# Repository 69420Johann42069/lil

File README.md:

# Farbmischer

Ein Geschenk: Tischgerät plus Web-App. Sie wählt eine Farbe am Handy (Farbwähler oder Foto antippen), das Gerät dosiert die passenden Mengen aus fünf günstigen Acryl-Grundfarben in einen Becher, sie rührt um. Gemerkte Farben lassen sich später exakt nachmischen.

## Entscheidungen

- Acrylfarbe aus fünf 60-ml-Spritzen: Primär-Cyan, Primär-Magenta, Primär-Gelb, Titanweiß, Schwarz
- Günstige Studienacryl in 500-ml-Flaschen als Vorrat, nachgefüllt wird direkt in die Spritze
- Bauform Stand 6: schwarzer Flakon mit Goldlinien, Ø 204 mm, 407 mm hoch, sechs Spritzen im Karussell, zwei Schrittmotoren, Dosieren nach Gewicht mit Wägezelle, Becher in einer Schublade. Ohne Licht, alles aus PETG gedruckt (auch Gold und Scheiben), keine Lackierung
- Bedienung nur im Browser, der ESP32 liefert die Seite selbst im WLAN aus
- Gerät dosiert nur, kein Rührwerk
- Elektronik auf Lochraster (zwei Treiber), Druckteile aus dem eigenen Drucker (Anycubic Kobra 2 Pro) in PETG

## Aufbau des Repos

| Pfad | Inhalt |
|---|---|
| `web/` | Web-App: Farbwahl, Foto, Rezept, gemerkte Farben, Kalibrierung, Gerätesteuerung |
| `firmware/` | PlatformIO-Projekt für den ESP32 |
| `hardware/` | Parameterblätter, OpenSCAD-Druckteile und Renderings (aktuell: Flakon Stand 8) |
| `electronics/` | `VERDRAHTUNG.md`: Verdrahtungsplan Stand 8 (Lochraster, Dupont). Die alte KiCad-Trägerplatine (Fünf-Motor-Variante) gilt nicht mehr |

## Stufen

| Stufe | Was | Status |
|---|---|---|
| 0 | Web-App: Farbe wählen, Rezept in Gramm, mit Küchenwaage abwiegen | fertig, getestet |
| 1 | Flakon mit zwei Motoren und Spritzenkarussell | Stand 8: Druckteile (OpenSCAD), Rendering, 56 Kollisionsprüfungen, Firmware (zwei Motoren, Wägezelle, Hall, Dosieren nach Gewicht, Host-Test der Rechenfunktionen), Web-App und Verdrahtungsplan fertig, Build mit `pio run` und alles auf Hardware nicht getestet |
| 2 | Kalibrierung mit Farbsensor | optional |

## Stufe 0: Web-App

1. `mixbox.js` herunterladen und nach `web/` legen. Quelle: Repository `scrtwpns/mixbox` auf GitHub, Datei `javascript/mixbox.js`. Lizenz CC BY-NC 4.0, für ein privates Geschenk in Ordnung, nicht für Verkauf. Die Datei steht in `.gitignore`.
2. `web/index.html` im Browser öffnen. Für das Handy im gleichen WLAN:

```
cd web
python3 -m http.server 8000
```

Dann am Handy `http://<IP des Rechners>:8000` aufrufen.

Funktionen: Farbwähler oder Hex-Wert, Farbe aus einem Foto antippen (Handykamera), Gesamtmenge in Gramm, Rezept mit Vorhersage-Swatch und Abweichung, Farben mit Namen merken und wieder laden, Primärfarben kalibrieren, Gerät steuern.

Die Farbmathematik liegt in `web/farbmath.js`: Mixbox mischt die Primärfarben im Latentraum, ein projizierter Gradientenabstieg sucht die Anteile mit kleinster Lab-Abweichung zur Zielfarbe.

### Primärfarben kalibrieren

Jede Grundfarbe satt auf weißes Papier streichen, trocknen lassen, bei Tageslicht fotografieren, Farbwert mit einer Pipette ablesen und in der App eintragen. Das verbessert die Rezepte deutlich, weil die Standardwerte nur grobe Schätzungen sind.

## Farben kaufen

Fünf Flaschen reichen für alles. Gesucht wird in Studienqualität (Flasche 250 bis 500 ml, meist unter 10 Euro):

| Spritze | Farbe | Suchbegriff beim Händler |
|---|---|---|
| C | Primär-Cyan | Primary Cyan, Primärblau, Cyan |
| M | Primär-Magenta | Primary Magenta, Primärrot, Magenta |
| Y | Primär-Gelb | Primary Yellow, Primärgelb |
| W | Titanweiß | Titanium White |
| K | Schwarz | Ivory Black oder Mars Black |

Nachfüllen: Kolben aus der Spritze ziehen, Farbe aus der Flasche einfüllen, Kolben wieder einsetzen, Düse nach oben, Luft rausdrücken. Flaschenfarbe ist dünner als Tubenfarbe und pumpt sich leichter.

## Stand 6: Flakon aus PETG, ohne Licht (aktuelles Konzept)

Entstanden aus der Kritik von vier Rollen (Kosten, Design, Ingenieur, Kunstliebhaberin), drei Konzepten und deren Bewertung (Stand 5.1), dann umgebaut auf den Wunsch „fast alles 3D-druckbar, keine LEDs, PETG“. Maßgeblich ist `hardware/farbmischer_parameter.md` mit Stückliste, Verdrahtung und dem Abschnitt für die Firmware. Rendering: `hardware/rendering_farbmischer.png`, Kollisionsprüfung: `python3 hardware/render_farbmischer.py --pruefung`, Druckteile: `hardware/farbmischer.scad` (Variable `teil`, jedes Teil liegt in Druckorientierung auf Z = 0; `openscad -o teil.stl -D 'teil="krone"' hardware/farbmischer.scad`). Gerät etwa 160 Euro, mit Startpaket und Farbe etwa 246 Euro.

Was sich gegenüber Stand 5.1 ändert: LEDs entfallen komplett (der Fortschritt steht nur in der App). Alles ist PETG, kein Spachteln, kein Lack, kein Anreibewachs. Gold sind gedruckte Gold-PETG-Teile (Goldring, Goldband, Kronenring, Portalrahmen in drei Leistenarten, Lippe, Buchsenring, Namensschild-Schrift). Portalscheibe (zwei Hälften) und Fensterscheiben sind gedruckt (Rauch- und Klar-PETG), der Ausleger mit Stempel ersetzt den Winkelstahl. Die Teilung des Körpers bei Z 235 ist eine gewollte Schattenfuge. Details in Abschnitt 0 des Parameterblatts.

**Stand 8 (Karussell direkt am Motor, Standard in `farbmischer.scad`):** Motor 2 sitzt mittig unter der Karussellplatte in einem gedruckten Kasten (Motorturm), kein Riemen, keine Welle, kein 70-Z-Rad, keine Pancake (beide Motoren sind derselbe NEMA 17, 34 mm). Filament zählt nicht mit. Aufbau auf Stand 7:

Schnelles Rendering Stand 8 (aus den OpenSCAD-Teilen, Scheiben undurchsichtig dargestellt): `hardware/rendering_stand8_aussen.png` und `hardware/rendering_stand8_schnitt.png` (Längsschnitt, Motorturm blau).

**Stand 7 Budget** (Schalter `budget`): ohne Feuchtrinne, Magnete an den Scheiben, gekaufte Linearlager und Gewindeeinsätze (Linearlager sind gedruckt, Ballast wird gratis mit Schrauben aus dem Arbeitsvorrat gefüllt; Portalscheiben, Fensterscheiben, Goldrahmen und Goldlippe bleiben, sie sind gedruckt und kosten nichts extra, die Scheiben werden geklebt), Gerät etwa 83 Euro, alles zusammen etwa 164 Euro, ohne Filament, Schrauben, Muttern, Scheiben und Kleber aus dem Arbeitsvorrat. Einkauf bei einem Shop (Amazon.de, Links, Preise teils unbelegt): `hardware/einkaufsliste_amazon.md`. Einkaufsliste mit Quellen und gekennzeichneten Schätzungen: `hardware/einkaufsliste.md`.

Filament für das ganze Gerät (Stand 6): PETG schwarz etwa 1,4 kg (am besten glänzend für Sockel und Front, matt für Körper und Krone), Gold 35 g, Rauch-PETG 50 g, Klar-PETG 25 g, weiß 40 g.

## Stufe 1: Revolver (Stand 4, abgelöst)

Zwei Schrittmotoren, fünf Spritzen in einem Karussell. Der Stößel sitzt fest über der vorderen Station, ein zweiter Motor zentral im Sockel dreht das Karussell direkt über eine Welle in der Mitte. Die Nutzerin wählt die Farbe, das Gerät dreht und dosiert alle Stationen nacheinander, am Ende nimmt sie den Becher heraus und rührt um. Säule Ø 170 mm, 48 cm hoch, Fenster unten vorne für den Becher, Rändelrand des Karussells durch einen Schlitz drehbar. Parameterblatt: `hardware/revolver_parameter.md`, Druckteile: `hardware/revolver.scad`, Rendering: `hardware/rendering_revolver.png`.

Vorbild aus der Recherche: das Hackaday-Projekt If Then Paint nutzt ein Spritzenkarussell mit fester Druckplatte (https://hackaday.io/project/166524). Zwei Lehren daraus: die Druckplatte darf nicht freitragend sein (dort hat sie sich bei 30-ml-Spritzen verbogen), und Acrylfarbe ist thixotrop, also nach dem Dosieren kurz warten, bevor der Stößel hochfährt. Einen Mechanismus, der mit einem Motor dreht und drückt (Malteserkreuz, Klinke), gibt es in der Literatur, aber kein DIY-Beispiel mit Spritzen; deshalb ein zweiter Motor für das Karussell, das ist einfacher und zuverlässiger.

Stößelkraft: NEMA 17 (0,4 Nm) an T8 mit 2 mm Steigung ergibt bei 30 % Wirkungsgrad rund 370 N, ein 60-ml-Kolben braucht bei zäher Farbe deutlich unter 100 N.

### Stückliste Revolver

| Teil | Menge | Woher |
|---|---|---|
| ESP32 DevKit V1 | 1 | Elektronikhändler |
| TMC2209 StepStick (oder A4988) | 2 | Elektronikhändler |
| NEMA 17, 40 mm | 2 | Stößel und Karussell |
| Stahlwelle Ø 8, 180 mm, mit Abflachung | 1 | 3D-Druck-Shop, Antriebswelle Karussell |
| T8-Spindel 2 mm Steigung, 150 mm, mit Flanschmutter | 1 | 3D-Druck-Shop |
| Linearwelle 8 mm, 150 mm, LM8UU | 1 plus 1 | 3D-Druck-Shop |
| Kugellager 608 | 2 | 3D-Druck-Shop |
| Kupplung 5 auf 8 mm | 2 | 3D-Druck-Shop |
| Mikro-Endschalter | 2 | einer oben, einer im Stößelfuß |
| Hall-Sensor A3144 | 1 | Referenz des Karussells |
| Magnet Ø 5 x 2 | 1 | Elektronikhändler |
| Stahlkugeln 6 mm (optional für das Karussell-Lager) | 24 | Baumarkt, Fahrradladen |
| Spritze 60 ml Luer-Lock | 5 plus Ersatz | Apotheke |
| Luer-Lock-Verschlusskappen | 10 | Apotheke |
| Netzteil 12 V 3 A mit Hohlstecker | 1 | Elektronikhändler |
| Buck-Modul 12 V auf 5 V | 1 | Elektronikhändler |
| LED-Ring WS2812 12 LEDs (optional) | 1 | Elektronikhändler |
| Lochrasterplatine, Buchsenleisten, Klemmen | | Elektronikhändler |
| Mischbecher Ø 56, Höhe 60 | 2 | Haushaltswaren |

Grob 80 bis 110 Euro. Die Trägerplatine aus `electronics/` ist für fünf Motoren ausgelegt, beim Revolver werden nur zwei Treiberplätze bestückt; Lochraster geht auch.

### Druckteile

`hardware/revolver.scad`, Variable `teil` für die einzelnen Teile, alle liegend ohne Stützen, höchstens 200 mm hoch für die Kobra 2 Pro (220 x 220 x 250). Ungerendert entstanden, `assert`-Prüfungen und nachzumessende Maße stehen in der Datei. Das ältere Konzept mit fünf Motoren (gerader Turm `spritzenpumpe.scad`, Säule `saeule_parameter.md`) bleibt als Referenz im Repo.

### Verdrahtung Revolver

| Signal | GPIO | Hinweis |
|---|---|---|
| STEP, DIR Stößel | 13, 33 | Treiber 1 |
| STEP, DIR Karussell | 14, 32 | Treiber 2 |
| ENABLE | 23 | beide Treiber |
| Endschalter oben | 18 | Schließer gegen GND, interner Pullup |
| Kontakt-Taster im Stößelfuß | 19 | Schließer gegen GND |
| Hall Referenz Karussell | 21 | digitaler Hall, Pullup |
| LED-Ring | 5 | WS2812 Daten |

### Für die Software-Sitzung

Die Firmware in `firmware/` ist noch für fünf Spritzenpumpen geschrieben. Für den Revolver ändert sich: Motor 1 Stößel, Motor 2 Karussell; Dosierung als Strecke nach Kontakt (Stößel fährt bis der Taster schließt, dann Gramm geteilt durch g_per_ml mal Schritte pro ml, danach 2 Sekunden warten, dann 2 mm hoch, dann ganz nach oben); Karussell referenziert beim Start per Hall-Sensor und fährt dann 40 Vollschritte je Station (Direktantrieb 1:1); vor jedem Drehen muss der Stößel am oberen Endschalter stehen; ein Rezept läuft vollautomatisch alle Stationen ab, am Ende Fertigmeldung und Zielfarbe auf dem LED-Ring. Details in `hardware/revolver_parameter.md`, Abschnitt „Was die Firmware wissen muss“.

### Firmware bauen und flashen

Unverändert, siehe `firmware/` (PlatformIO). Die Kalibrierung per Waage bleibt gleich: 5 ml ausdrücken, wiegen, `g_per_ml` setzen.

### Bekannte Hürde

Acryl härtet an der Düse in Minuten. Düsen nach jeder Session abwischen und mit Luer-Kappen verschließen. Die vier inaktiven Düsen tropfen in die Abtropfschale im Sockel, die sich herausnehmen und abwaschen lässt.

## Offene Punkte

- Ausleger aus PETG mit 250 N belasten (Nachweis steht im Parameterblatt, Abschnitt 16), Rauch- und Klarscheibe als Probe drucken, Goldleisten als Probe kleben (Abschnitt 17)
- Spritzenmaße nachmessen und Druckteile einer Station probeweise drucken
- Firmware auf zwei Motoren (Stößel, Karussell), Dosieren nach Gewicht und ohne LEDs umstellen (Software-Sitzung)
- Karussell-Lagerung testen: Gleitlager PETG auf PETG oder Stahlkugeln in der Rille, Reibung muss unter dem Motormoment bleiben
- Erster Hardwaretest ohne Farbe: Referenzfahrten beider Motoren, Kontakt-Taster, 40 Schritte je Station prüfen

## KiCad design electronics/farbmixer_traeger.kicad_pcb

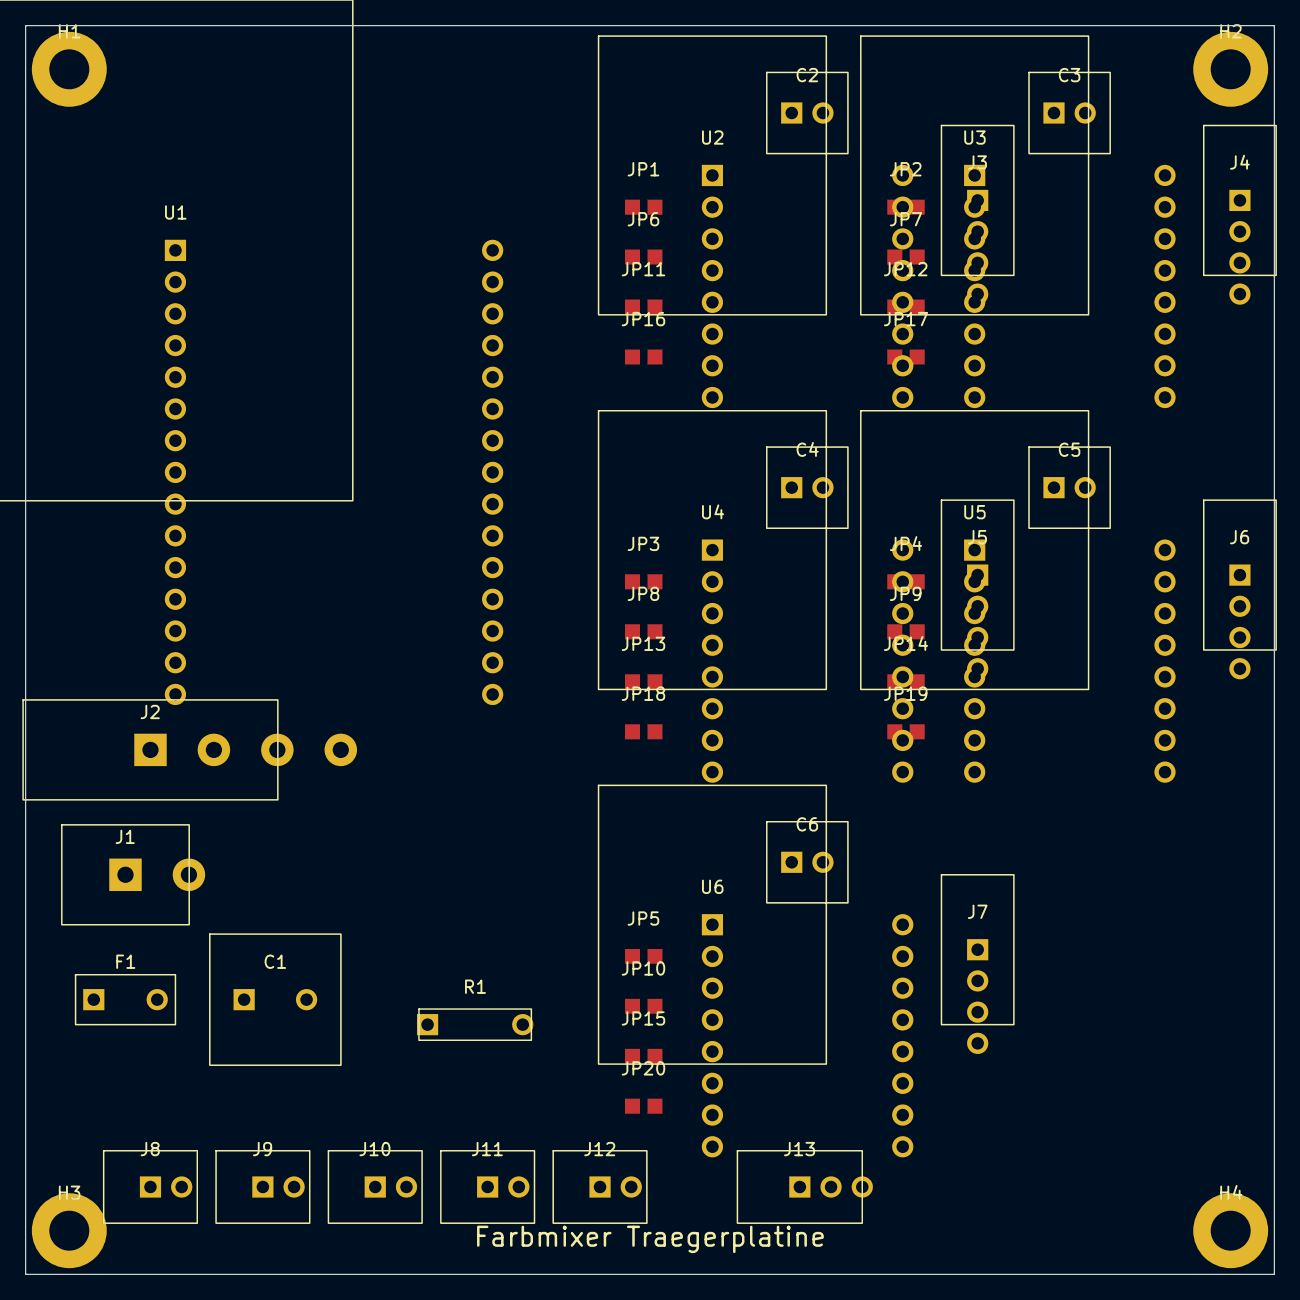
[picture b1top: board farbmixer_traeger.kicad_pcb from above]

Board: 2 copper layers, 100.0 x 100.0 mm, 51 parts (0 on the bottom side), 67 nets, no tracks yet.

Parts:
C1: 470u 25V; C_Radial_5.0
C2, C3, C4, C5, C6: 100u 25V; C_Radial_2.5
F1: Polyfuse 3A; Fuse_Radial_5.08
H1, H2, H3, H4: M3; MountingHole_3.2
J1: 12V IN 5.08; Terminal_2_5.08
J2: Buck 12V->5V 5.08; Terminal_4_5.08
J3: Motor 1 XH-4; JST_XH_4
J4: Motor 2 XH-4; JST_XH_4
J5: Motor 3 XH-4; JST_XH_4
J6: Motor 4 XH-4; JST_XH_4
J7: Motor 5 XH-4; JST_XH_4
J8: Endstop 1 XH-2; JST_XH_2
J9: Endstop 2 XH-2; JST_XH_2
J10: Endstop 3 XH-2; JST_XH_2
J11: Endstop 4 XH-2; JST_XH_2
J12: Endstop 5 XH-2; JST_XH_2
J13: LED-Ring XH-3; JST_XH_3
JP1, JP2, JP3, JP4, JP5, JP6, JP7, JP8, JP9, JP10, JP11, JP12, JP13, JP14, JP15, JP16, JP17, JP18, JP19, JP20: SJ; SolderJumper
R1: 10k; R_Axial_7.62
U1: ESP32 DevKit V1 30p; ESP32_DevKit_30
U2: StepStick 1; StepStick
U3: StepStick 2; StepStick
U4: StepStick 3; StepStick
U5: StepStick 4; StepStick
U6: StepStick 5; StepStick

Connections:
+3V3: JP1.2, JP2.2, JP3.2, JP4.2, JP5.2, JP6.2, JP7.2, JP8.2, JP9.2, JP10.2, JP11.2, JP12.2, JP13.2, JP14.2, JP15.2, R1.2, U1.1, U2.15, U3.15, U4.15, U5.15, U6.15
+5V: J2.3, J13.1, U1.16
+12V: C1.1, C2.1, C3.1, C4.1, C5.1, C6.1, F1.2, J2.1, U2.9, U3.9, U4.9, U5.9, U6.9
+12V_IN: F1.1, J1.1
GND: C1.2, C2.2, C3.2, C4.2, C5.2, C6.2, J1.2, J2.2, J2.4, J8.2, J9.2, J10.2, J11.2, J12.2, J13.2, U1.14, U1.17, U2.10, U2.16, U3.10, U3.16, U4.10, U4.16, U5.10, U5.16, U6.10, U6.16
GPIO4: U1.28, U4.8
GPIO5: J13.3, U1.25
GPIO13: U1.15, U2.7
GPIO14: U1.12, U3.7
GPIO16: U1.27, U5.8
GPIO17: U1.26, U6.8
GPIO18: J8.1, U1.24
GPIO19: J9.1, U1.23
GPIO21: J10.1, U1.22
GPIO22: J11.1, U1.19
GPIO23: U1.18, U2.1, U3.1, U4.1, U5.1, U6.1
GPIO25: U1.9, U6.7
GPIO26: U1.10, U5.7
GPIO27: U1.11, U4.7
GPIO32: U1.7, U3.8
GPIO33: U1.8, U2.8
GPIO34: J12.1, R1.1, U1.5
M1_1A: J3.1, U2.13
M1_1B: J3.2, U2.14
M1_2A: J3.3, U2.12
M1_2B: J3.4, U2.11
M2_1A: J4.1, U3.13
M2_1B: J4.2, U3.14
M2_2A: J4.3, U3.12
M2_2B: J4.4, U3.11
M3_1A: J5.1, U4.13
M3_1B: J5.2, U4.14
M3_2A: J5.3, U4.12
M3_2B: J5.4, U4.11
M4_1A: J6.1, U5.13
M4_1B: J6.2, U5.14
M4_2A: J6.3, U5.12
M4_2B: J6.4, U5.11
M5_1A: J7.1, U6.13
M5_1B: J7.2, U6.14
M5_2A: J7.3, U6.12
M5_2B: J7.4, U6.11
MS1_1: JP1.1, U2.2
MS1_2: JP2.1, U3.2
MS1_3: JP3.1, U4.2
MS1_4: JP4.1, U5.2
MS1_5: JP5.1, U6.2
MS2_1: JP6.1, U2.3
MS2_2: JP7.1, U3.3
MS2_3: JP8.1, U4.3
MS2_4: JP9.1, U5.3
MS2_5: JP10.1, U6.3
MS3_1: JP11.1, U2.4
MS3_2: JP12.1, U3.4
MS3_3: JP13.1, U4.4
MS3_4: JP14.1, U5.4
MS3_5: JP15.1, U6.4
RST_1: JP16.1, U2.5
RST_2: JP17.1, U3.5
RST_3: JP18.1, U4.5
RST_4: JP19.1, U5.5
RST_5: JP20.1, U6.5
SLP_1: JP16.2, U2.6
SLP_2: JP17.2, U3.6
SLP_3: JP18.2, U4.6
SLP_4: JP19.2, U5.6
SLP_5: JP20.2, U6.6
